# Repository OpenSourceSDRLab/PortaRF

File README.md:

# PortaRF
Custom Hardware and Firmware Bin Files for the PortaRF Gadget.

# Introduction
The PortaRF is an open-source hardware platform that combines the [HackRF One R10](https://github.com/greatscottgadgets/hackrf/tree/master/hardware/hackrf-one) and [PortaPack H4M](https://github.com/OpenSourceSDRLab/mayhem-firmware/tree/next/hardware/portapack_h4m) into a single Board. It supports the transmission and reception of radio signals ranging from 1 MHz to 6 GHz, rendering it an exceptionally versatile tool for RF exploration and development.  It is a portable, standalone device for signal analysis and transmission without requiring a computer.

Here is a news report about the PortaRF from [RTL-SDR.com](https://www.rtl-sdr.com/two-youtube-reviews-of-the-new-portarf-a-new-hackrf-portapack-combo/).

# Where to buy
[OpenSourceSDRLab](https://opensourcesdrlab.com/products/portarf) official website.

# Videos

)

# Hardware Improvements
1. **Doubled flash storage capacity**.
We have replaced the original W25Q80DVSSIQ with W25Q16DV SPI Flash chip, expanding the original firmware storage capacity from 1M byte to 2M byte. This provides a broader creative space for Mayhem firmware developers, enabling the implementation of more complex signal processing algorithms and functions.

2. **4.0-inch IPS resistive touch screen**.
The screen has been upgraded to a 4.0-inch IPS full-view high-definition display. Compared with the original 3.2-inch non-IPS matte screen, it has made a significant improvement in color reproduction, viewing angle and touch accuracy. Whether it's spectrum analysis or parameter settings, the text is clearer and the operation is more precise.

3. **3000mAh lithium battery system**.
The battery capacity has been increased to 3000mAh, significantly extending the battery life. At the same time, an intelligent battery protection board has been used in this battery, providing protection against overcharging, overdischarging, short circuiting, and overcurrent. This lithium battery is produced by a legitimate factory with guaranteed quality.

4. **User-friendly hand-held directional keys**.
PortaRF has added a gamepad-style directional button. It is particularly suitable for rapid directional operations in functions such as spectrum scanning and game applications. It will significantly enhance the direction control efficiency and comfort.

5. **Modular Expansion Board Design**.
The expansion board adopts a Board to Board connector, a socket interface similar to the memory module, which is smaller in size and more stable in installation. This can optimize the internal space utilization.

6. **Light Guide Column LED Status Indication System**.
PortaRF also incorporates the light guide column design, making the LED status lights more visible. Regardless of day or night, the equipment status is clearly visible.

7. **Nice shell design**.
We have designed a brand new shell for the PortaRF and added many design elements, such as the buckle of the shell, which makes the shell fit tightly. The slot of the memory card is designed with grooves, the SD card can be inserted and removed without the need for tools. The dual speaker sound hole design enables better sound output from the speakers.

8. **AI voice-assisted (Beta version)**.
PortaRF incorporates voice-controlled interaction technology. Users can perform operations such as device activation, application switching, and system reboot through natural voice commands. This feature is particularly suitable for scenarios where hands are not available, providing additional convenience operations.

# Applications
<div class="editor_table_wrap">&nbsp;
<table border="1" style="width: 81.0373%; height: 526px;">
<tbody>
<tr style="height: 26.2px;">
<td style="width: 55.25%; height: 26.2px;">
<h3 class="text-xl font-semibold text-indigo-800 mb-3">Receive Applications</h3>
</td>
<td style="width: 44.7339%; height: 26.2px;">
<h3 class="text-xl font-semibold text-indigo-800 mb-3">Transmit Applications</h3>
</td>
</tr>
<tr style="height: 22.4px;">
<td style="width: 55.25%; height: 22.4px;"><strong>Sniff &amp; Capture</strong>: Sniff &amp; capture signals for instant replay or save to SD card for analysis</td>
<td style="width: 44.7339%; height: 22.4px;"><strong>ADS-B</strong>: Transmit ADS-B (Aviation) signals for testing</td>
</tr>
<tr style="height: 44.8px;">
<td style="width: 55.25%; height: 44.8px;"><strong>ADS-B</strong>: Receive and analyze aviation signals with real-time location display</td>
<td style="width: 44.7339%; height: 44.8px;"><strong>APRS</strong>: Transmit APRS packets for GPS, weather stations and telemetry</td>
</tr>
<tr style="height: 22.4px;">
<td style="width: 55.25%; height: 22.4px;"><strong>AIS</strong>: Receive and analyze marine vessel signals</td>
<td style="width: 44.7339%; height: 22.4px;"><strong>GPS</strong>: Transmit GPS signals for testing</td>
</tr>
<tr style="height: 22.4px;">
<td style="width: 55.25%; height: 22.4px;"><strong>AFSK</strong>: Receive, demodulate and analyze AFSK signals</td>
<td style="width: 44.7339%; height: 22.4px;"><strong>Key Fob</strong>: Key-fob capture, replay and emulation for multiple models</td>
</tr>
<tr style="height: 22.4px;">
<td style="width: 55.25%; height: 22.4px;"><strong>Bluetooth</strong>: Sniff MAC addresses of BLE devices</td>
<td style="width: 44.7339%; height: 22.4px;"><strong>Morse Code</strong>: Morse code transmission tool</td>
</tr>
<tr style="height: 22.4px;">
<td style="width: 55.25%; height: 22.4px;"><strong>NRF</strong>: Decode NRF24L01 signals, commonly used for drones</td>
<td style="width: 44.7339%; height: 22.4px;"><strong>Burger Pager</strong>: Transmit restaurant pager signals</td>
</tr>
<tr style="height: 22.4px;">
<td style="width: 55.25%; height: 22.4px;"><strong>Audio</strong>: Decode WFM/NFM/AM radio transmissions</td>
<td style="width: 44.7339%; height: 22.4px;"><strong>POCSAG</strong>: Transmit pager signals</td>
</tr>
<tr style="height: 22.4px;">
<td style="width: 55.25%; height: 22.4px;"><strong>Spectrum Analyzer</strong>: Waterfall spectrum analyzer for detecting signals</td>
<td style="width: 44.7339%; height: 22.4px;"><strong>SSTV</strong>: Transmit Slow Scan Television signals</td>
</tr>
<tr style="height: 22.4px;">
<td style="width: 55.25%; height: 22.4px;"><strong>Analog TV</strong>: Decode and watch analog TV signals, used on FPV drones</td>
<td style="width: 44.7339%; height: 22.4px;"><strong>RDS</strong>: Send Radio Data System messages</td>
</tr>
<tr style="height: 22.4px;">
<td style="width: 55.25%; height: 22.4px;"><strong>ERT Meters</strong>: Decode ERT Meter signals</td>
<td style="width: 44.7339%; height: 22.4px;"><strong>OOK</strong>: Send On-Off Keying packages</td>
</tr>
<tr style="height: 22.4px;">
<td style="width: 55.25%; height: 22.4px;"><strong>POCSAG</strong>: Sniff and decode pager signals</td>
<td style="width: 44.7339%; height: 22.4px;"></td>
</tr>
<tr style="height: 22.4px;">
<td style="width: 55.25%; height: 22.4px;"><strong>Radiosonde</strong>: Sniff and decode weather station signals</td>
<td style="width: 44.7339%; height: 22.4px;"></td>
</tr>
<tr style="height: 22.4px;">
<td style="width: 55.25%; height: 22.4px;"><strong>TPMS</strong>: Decode Tire Pressure Monitoring System sensors</td>
<td style="width: 44.7339%; height: 22.4px;">&nbsp; &nbsp; &nbsp; &nbsp;</td>
</tr>
</tbody>
</table>

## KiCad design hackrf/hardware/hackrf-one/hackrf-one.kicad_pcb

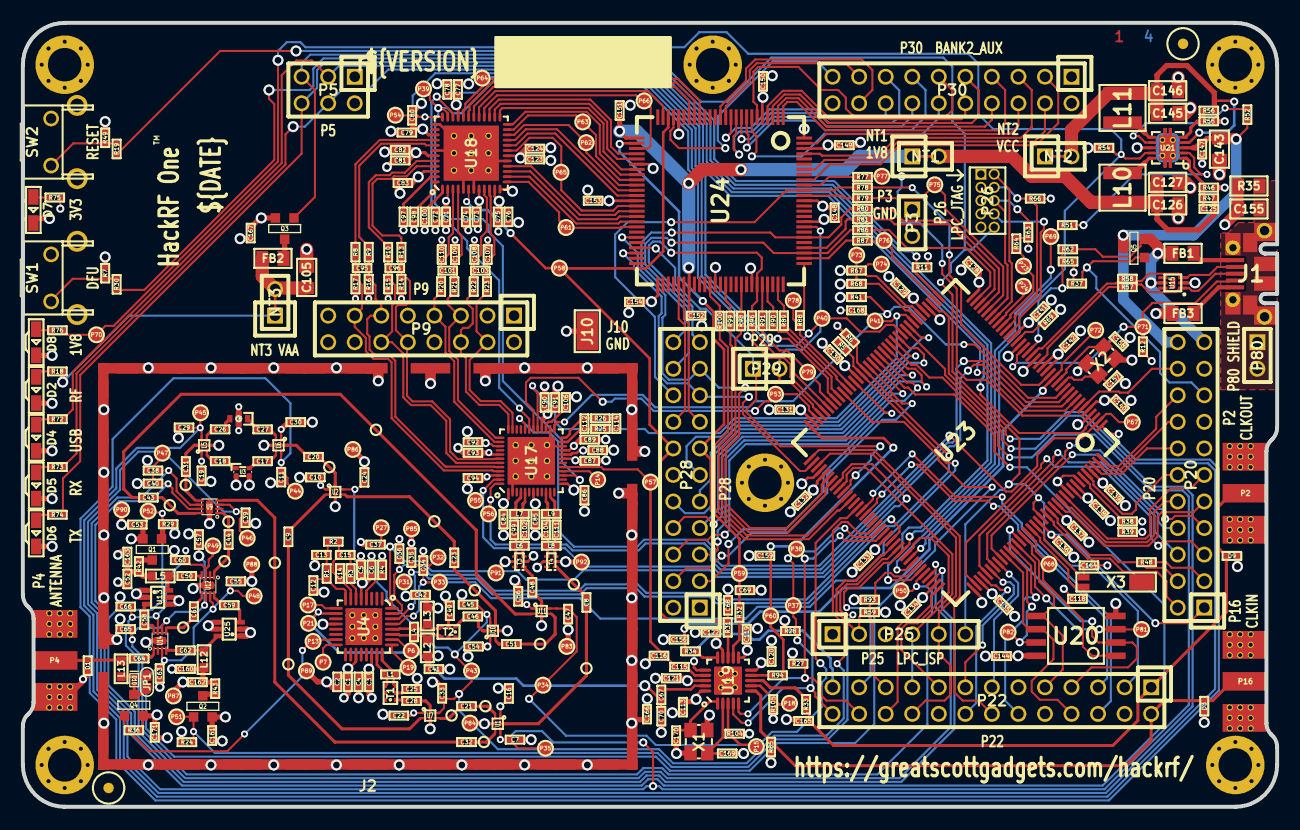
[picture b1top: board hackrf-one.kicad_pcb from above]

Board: 4 copper layers, 120.0 x 75.0 mm, 437 parts (0 on the bottom side), 319 nets.

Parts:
C1, C3, C5, C7, C11, C24, C29, C33, C34, C35, C36, C37, C38, C39, C40, C45, C47, C55, C57, C60, C63, C65, C66, C67, C115, C125: 33pF; GSG-0402
C2, C4, C6, C10, C16, C19, C22, C30, C54, C56, C87, C88, C89, C92, C93, C162, C163: 10nF; GSG-0402
C8, C21, C32, C43, C48, C51, C84, C85, C86, C94, C95, C96, C99, C101, C102, C103, C107, C108, C109, C110: 22pF; GSG-0402
C9, C17, C18, C20, C23, C25, C28, C31, C44, C46, C49, C50, C58, C59, C61, C62, C64, C71, C73, C75, C77, C79, C81, C83, C91, C113, C119, C120, C121, C122, C123, C128, C129, C130, C131, C132, C133, C134, C135, C136, C137, C138, C139, C140, C141, C142, C144, C147, C148, C149, C150, C151, C152, C153, C154, C166, C167: 100nF; GSG-0402
C12, C13: 330pF; GSG-0402
C14: 8p2; GSG-0402
C15, C112: 180pF; GSG-0402
C26, C27, C116, C156: 47pF; GSG-0402
C41, C42, C52, C68, C69, C70, C90, C159, C160, C165, C168: 100pF; GSG-0402
C53, C106, C161, C171: 1uF; GSG-0402
C72, C74, C76, C78, C80, C82, C124: 2.2uF; GSG-0402
C97, C98, C100: 330nF; GSG-0402
C104, C111: 3pF; GSG-0402
C105, C126, C127, C143, C145, C146: 10uF; GSG-0805
C114: 3.3nF; GSG-0402
C118, C157, C158, C164: 18pF; GSG-0402
C155: DNP; GSG-0805
C169, C170: 1.8pF; GSG-0402
D1, D3, D9: GSG-DIODE-TVS-BI; GSG-0402
D2: VAALED; LTST-S220
D4: USBLED; LTST-S220
D5: RXLED; LTST-S220
D6: TXLED; LTST-S220
D7: VCCLED; LTST-S220
D8: 1V8LED; LTST-S220
D10: D_Schottky; DSN1006-2
FB1, FB2, FB3: FILTER; GSG-0805
FID1, FID2: FIDUCIAL; GSG-MARK1MM
J1: USB-MICRO-B; GSG-USB-MICROB-FCI-10103592-EXT
J2: RF-SHIELD-FRAME; GSG-SHIELD-BMI-S-230
J4, J5, J6, J7, J8, J9: MOUNTING_HOLE; GSG-HOLE126MIL-COPPER
J10: GND_CLIP; GSG-TEST-POINT-S1751-46R
JP1: Jumper; 0603-JUMPER
L1, L4, L6, L8, L9: DNP; GSG-0402
L2, L3, L5, L12, L13: 10uH; GSG-0603
L7: 6.2nH; GSG-0402
L10, L11: 4u7; GSG-NRG4026
NT1: 1V8; HEADER-1x2-SHORTED
NT2: VCC; HEADER-1x2-SHORTED
NT3: VAA; HEADER-1x2-SHORTED
P2: CLKOUT; GSG-SMA-73251-2120
P3: GND; GSG-HEADER-NOMARK-1x2
P4: ANTENNA; GSG-SMA-73251-2120
P5: LEDS; GSG-HEADER-2x3
P6: GPO4; GSG-TESTPOINT-50MIL
P7: GPO2; GSG-TESTPOINT-50MIL
P9: BASEBAND; GSG-HEADER-2x8
P13: GPO1; GSG-TESTPOINT-50MIL
P14: XCVR_CLKOUT; GSG-TESTPOINT-50MIL
P15: INTR; GSG-TESTPOINT-50MIL
P16: CLKIN; GSG-SMA-73251-2120
P17: GPO6; GSG-TESTPOINT-50MIL
P18: OEB; GSG-TESTPOINT-50MIL
P19: GPO3; GSG-TESTPOINT-50MIL
P20: GPIO; GSG-HEADER-2x11
P21: REF_IN; GSG-TESTPOINT-50MIL
P22: I2S; GSG-HEADER-2x13
P23: DBGEN; GSG-TESTPOINT-50MIL
P24: TRST; GSG-TESTPOINT-50MIL
P25: LPC_ISP; GSG-HEADER-1x6
P26: LPC_JTAG; GSG-50MIL-HEADER-2x5-TH
P27: MIXER_SDATA; GSG-TESTPOINT-50MIL
P28: SD; GSG-HEADER-2x11
P29: CPLD_JTAG; GSG-HEADER-1x2
P30: BANK2_AUX; GSG-HEADER-2x10
P31: MIXER_SCLK; GSG-TESTPOINT-50MIL
P32: MIXER_ENX; GSG-TESTPOINT-50MIL
P33: MIXER_RESETX; GSG-TESTPOINT-50MIL
P34: MIX_BYPASS; GSG-TESTPOINT-50MIL
P35: !MIX_BYPASS; GSG-TESTPOINT-50MIL
P37: SCL; GSG-TESTPOINT-50MIL
P38: SDA; GSG-TESTPOINT-50MIL
P39: SSP1_SCK; GSG-TESTPOINT-50MIL
P40: SSP1_COPI; GSG-TESTPOINT-50MIL
P41: SSP1_CIPO; GSG-TESTPOINT-50MIL
P43: RX; GSG-TESTPOINT-50MIL
P44: HP; GSG-TESTPOINT-50MIL
P45: LP; GSG-TESTPOINT-50MIL
P46: TX_MIX_BP; GSG-TESTPOINT-50MIL
P47: RX_MIX_BP; GSG-TESTPOINT-50MIL
P48: TX_AMP; GSG-TESTPOINT-50MIL
P49: RX_AMP; GSG-TESTPOINT-50MIL
P50: AMP_BYPASS; GSG-TESTPOINT-50MIL
P51: !TX_AMP_PWR; GSG-TESTPOINT-50MIL
P52: !RX_AMP_PWR; GSG-TESTPOINT-50MIL
P53: CS_XCVR; GSG-TESTPOINT-50MIL
P54: CS_AD; GSG-TESTPOINT-50MIL
P55: TXENABLE; GSG-TESTPOINT-50MIL
P56: RXENABLE; GSG-TESTPOINT-50MIL
P57: XTAL2; GSG-TESTPOINT-50MIL
P58: GCK1; GSG-TESTPOINT-50MIL
P59: GCK2; GSG-TESTPOINT-50MIL
P60: SGPIO_CLK; GSG-TESTPOINT-50MIL
P61: DA0; GSG-TESTPOINT-50MIL
P62: DA7; GSG-TESTPOINT-50MIL
P63: DD0; GSG-TESTPOINT-50MIL
P64: DD9; GSG-TESTPOINT-50MIL
P65: DA4; GSG-TESTPOINT-50MIL
P66: DD5; GSG-TESTPOINT-50MIL
P67: RSSI; GSG-TESTPOINT-50MIL
P68: SPIFI_CS; GSG-TESTPOINT-50MIL
P69: VREGMODE; GSG-TESTPOINT-50MIL
P70: EN_1V8; GSG-TESTPOINT-50MIL
P71: ID; GSG-TESTPOINT-50MIL
P72: GP_CLKIN; GSG-TESTPOINT-50MIL
P73: P1_2; GSG-TESTPOINT-50MIL
P74: P1_1; GSG-TESTPOINT-50MIL
P75: SGPIO0; GSG-TESTPOINT-50MIL
P76: SGPIO7; GSG-TESTPOINT-50MIL
P77: SGPIO9; GSG-TESTPOINT-50MIL
P78: SGPIO10; GSG-TESTPOINT-50MIL
P79: SGPIO11; GSG-TESTPOINT-50MIL
P80: SHIELD; GSG-HEADER-NOMARK-1x2
P81: SPIFI_SIO2; GSG-TESTPOINT-50MIL
P82: SPIFI_SIO3; GSG-TESTPOINT-50MIL
P83, P84, P85, P86, P87, P88, P89, P90, P91, P92: GND; GSG-TESTPOINT-50MIL
Q1, Q2, Q3, Q4, Q5: MOSFET_P; SOT23-3
R1, R2, R72, R75: 470; GSG-0402
R3: 22k; GSG-0402
R4: 51k; GSG-0402
R5, R6, R7, R11, R12, R24, R29, R36, R37, R41, R48, R49, R51, R52, R54, R59, R62, R63, R64, R66, R67, R68, R85, R93, R104, R105: 10k; GSG-0402
R8, R9, R10, R13, R73, R76: 1k; GSG-0402
R14, R15, R16, R17: 4k7; GSG-0402
R18, R27, R28, R74: 1k8; GSG-0402
R19, R30, R31, R32, R33, R34, R77, R78, R79, R80, R81, R86, R87, R88, R89, R90, R91, R94, R96, R98, R99, R100: 39; GSG-0402
R20, R21, R22, R23, R57, R58: 0; GSG-0402
R25, R26: 475; GSG-0402
R35: DNP; GSG-0805
R38: 15.4k; GSG-0402
R39, R47: 330k; GSG-0402
R42, R43: 18; GSG-0402
R46, R55: 162k; GSG-0402
R56: 715k; GSG-0402
R65: 18k; GSG-0402
R69: 12k; GSG-0402
SW1: DFU; GSG-SWITCH-FSMRA
SW2: RESET; GSG-SWITCH-FSMRA
T1: MIX_IN_BALUN; GSG-B0310J50100AHF
T2: MIX_OUT_BALUN; GSG-B0310J50100AHF
T3: RX_BALUN; GSG-2500BL14M100
T4: TX_BALUN; GSG-2500BL14M100
TESTPOINT-30MIL-MASKONLY, TESTPOINT-30MIL-MASKONLY#2, TESTPOINT-30MIL-MASKONLY#3, TESTPOINT-30MIL-MASKONLY#4, TESTPOINT-30MIL-MASKONLY#5, TESTPOINT-30MIL-MASKONLY#6, TESTPOINT-30MIL-MASKONLY#7, TESTPOINT-30MIL-MASKONLY#8, TESTPOINT-30MIL-MASKONLY#9, TESTPOINT-30MIL-MASKONLY#10, TESTPOINT-30MIL-MASKONLY#11, TESTPOINT-30MIL-MASKONLY#12, TESTPOINT-30MIL-MASKONLY#13, TESTPOINT-30MIL-MASKONLY#14, TESTPOINT-30MIL-MASKONLY#15, TESTPOINT-30MIL-MASKONLY#16, TESTPOINT-30MIL-MASKONLY#17: VAL**; GSG-TESTPOINT-30MIL-MASKONLY
U1, U2, U5, U6, U7, U10, U11: SKY13453; SKY13350-385LF
U3: LOWPASS_FILTER; GSG-LP0603
U4: RFFC5072; GSG-QFN32
U8: HIGHPASS_FILTER; GSG-HP-DEA
U9, U12, U14: SKY13317; GSG-SKY13317-373LF
U13, U25: MGA-81563; GSG-SOT363
U15: TVS; GSG-LXES1TBCC2-004
U17: MAX2837; GSG-QFN48-6
U18: MAX5864; GSG-QFN48-7
U19: SI5351C; GSG-QFN20-4
U20: W25Q80; GSG-SOIC8-208
U21: TPS62410; GSG-S-PVSON-N10
U23: LPC4320FBD144; GSG-LQFP144
U24: GSG-XC2C64A-7VQG100C; GSG-VQ100
X1: MAIN_XTAL; GSG-XTAL3.2x2.5mm
X2: MCU_XTAL; GSG-XTAL3.2x2.5mm
X3: RTC_XTAL; GSG-XTAL-AB26TRQ

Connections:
!MIX_BYPASS: C7.2, C38.2, P35.1, U1.5 (VCTL), U9.6 (V2), U23.50 (P1_7)
!RX_AMP_PWR: P52.1, Q1.1 (G), R29.2, U23.106 (P2_12)
!TX_AMP_PWR: P51.1, Q2.1 (G), R24.1, U23.97 (P6_9)
!VAA_ENABLE: P5.5, Q3.1 (G), R11.2, U23.37 (P5_0)
+1V8: C151.1, C152.1, NT1.1, U24.26 (VCC), U24.57 (VCC)
/baseband/CLK0: R31.2, U19.13 (CLK0)
/baseband/CLK1: R32.2, U19.12 (CLK1)
/baseband/CLK2: R94.2, U19.9 (CLK2)
/baseband/CLK3: R33.2, U19.8 (CLK3)
/baseband/CLK5: C115.1, U19.17 (CLK5)
/baseband/COM: C97.1, U18.47 (COM)
/baseband/CPOUT+: C112.2, R25.1, U17.23 (CPOUT+)
/baseband/CPOUT-: C112.1, R26.1, U17.24 (CPOUT-)
/baseband/IA+: C101.1, C110.1, R20.1, U18.3 (IA+)
/baseband/IA-: C101.2, C109.1, R21.1, U18.4 (IA-)
/baseband/ID+: R13.1, U18.45 (ID+)
/baseband/ID-: R10.1, U18.44 (ID-)
/baseband/INTR: P15.1, R104.2, U19.3 (INTR)
/baseband/OEB: P18.1, R105.2, U19.7 (OEB)
/baseband/QA+: C103.2, C107.1, R23.1, U18.10 (QA+)
/baseband/QA-: C103.1, C108.1, R22.1, U18.9 (QA-)
/baseband/QD+: R8.1, U18.40 (QD+)
/baseband/QD-: R9.1, U18.41 (QD-)
/baseband/REFN: C98.1, U18.48 (REFN)
/baseband/REFP: C100.1, U18.1 (REFP)
/baseband/RXBBI+: P9.7, R20.2, U17.38 (RXBBI+)
/baseband/RXBBI-: P9.5, R21.2, U17.37 (RXBBI-)
/baseband/RXBBQ+: P9.6, R22.2, U17.36 (RXBBQ+)
/baseband/RXBBQ-: P9.4, R23.2, U17.35 (RXBBQ-)
/baseband/TXBBI+: C96.1, P9.12, R10.2, R15.1, U17.43 (TXBBI+)
/baseband/TXBBI-: C96.2, P9.10, R13.2, R14.1, U17.42 (TXBBI-)
/baseband/TXBBQ+: C95.2, P9.11, R9.2, R16.1, U17.44 (TXBBQ+)
/baseband/TXBBQ-: C95.1, P9.13, R8.2, R17.1, U17.45 (TXBBQ-)
/baseband/XA: C170.2, U19.1 (XA), X1.3
/baseband/XB: C169.2, U19.2 (XB), X1.1
/baseband/XCVR_CLKOUT: P14.1, U17.16 (CLOCKOUT)
/baseband/XTAL2: C115.2, C116.1, P57.1, U17.17 (XTAL2)
/frontend/!ANT_BIAS: P13.1, Q4.1 (G), R36.1, U4.15 (GPO1/ADD1)
/frontend/REF_IN: C67.2, C70.1, P21.1, U4.10 (REF_IN)
/frontend/RX_AMP_IN: C58.1, U14.8 (RF3)
/frontend/RX_AMP_OUT: C50.2, U12.4 (RF1)
/frontend/TX_AMP_IN: C59.1, U12.8 (RF3)
/frontend/TX_AMP_OUT: C62.1, U14.4 (RF1)
/mcu/usb/power/ADC0_0: P20.20, U23.6 (ADC0_0/ADC1_0/DAC)
/mcu/usb/power/ADC0_2: P20.16, U23.143 (ADC0_2/ADC1_2)
/mcu/usb/power/ADC0_3: R38.2, R39.1, U23.139 (ADC0_3/ADC1_3)
/mcu/usb/power/ADC0_5: P20.18, U23.144 (ADC0_5/ADC1_5)
/mcu/usb/power/ADC0_6: P20.14, U23.142 (ADC0_6/ADC1_6)
/mcu/usb/power/B1AUX13: P28.16, U24.55 (BANK1F4M13)
/mcu/usb/power/B1AUX14: P28.15, U24.56 (BANK1F4M14)
/mcu/usb/power/B2AUX1: P30.18, U24.13 (BANK2F1M1)
/mcu/usb/power/B2AUX2: P30.17, U24.12 (BANK2F1M2)
/mcu/usb/power/B2AUX3: P30.16, U24.11 (BANK2F1M3)
/mcu/usb/power/B2AUX4: P30.15, U24.10 (BANK2F1M4)
/mcu/usb/power/B2AUX5: P30.14, U24.9 (BANK2F1M5)
/mcu/usb/power/B2AUX6: P30.13, U24.8 (BANK2F1M6)
/mcu/usb/power/B2AUX7: P30.12, U24.7 (BANK2F1M7)
/mcu/usb/power/B2AUX8: P30.11, U24.6 (BANK2F1M8)
/mcu/usb/power/B2AUX9: P30.10, U24.4 (BANK2F1M9)
/mcu/usb/power/B2AUX10: P30.9, U24.3 (BANK2F1M10)
/mcu/usb/power/B2AUX11: P30.8, U24.2 (BANK2F1M11)
/mcu/usb/power/B2AUX12: P30.7, U24.1 (BANK2F1M12)
/mcu/usb/power/B2AUX13: P30.6, U24.99 (BANK2F1M13)
/mcu/usb/power/B2AUX14: P30.5, U24.97 (BANK2F1M14)
/mcu/usb/power/B2AUX15: P30.4, U24.94 (BANK2F1M15)
/mcu/usb/power/B2AUX16: P30.3, U24.92 (BANK2F1M16)
/mcu/usb/power/BANK2F3M1: R77.2, U24.91 (BANK2F3M1)
/mcu/usb/power/BANK2F3M2: P28.18, R78.2, U24.90 (BANK2F3M2)
/mcu/usb/power/BANK2F3M3: R79.2, U24.89 (BANK2F3M3)
/mcu/usb/power/BANK2F3M4: P28.22, R80.2, U24.81 (BANK2F3M4)
/mcu/usb/power/BANK2F3M5: R81.2, U24.79 (BANK2F3M5)
/mcu/usb/power/BANK2F3M6: P28.20, R86.2, U24.78 (BANK2F3M6)
/mcu/usb/power/BANK2F3M7: R87.2, U24.77 (BANK2F3M7)
/mcu/usb/power/BANK2F3M8: R88.2, U24.76 (BANK2F3M8)
/mcu/usb/power/BANK2F3M9: R89.2, U24.74 (BANK2F3M9)
/mcu/usb/power/BANK2F3M10: R90.2, U24.72 (BANK2F3M10)
/mcu/usb/power/BANK2F3M11: R91.2, U24.71 (BANK2F3M11)
/mcu/usb/power/BANK2F3M12: P28.21, R96.2, U24.70 (BANK2F3M12)
/mcu/usb/power/BANK2F3M14: R98.2, U24.67 (BANK2F3M14)
/mcu/usb/power/BANK2F3M15: R99.2, U24.64 (BANK2F3M15)
/mcu/usb/power/BANK2F3M16: R100.2, U24.61 (BANK2F3M16)
/mcu/usb/power/CPLD_TCK: P28.17, U23.74 (P6_1), U24.48 (TCK)
/mcu/usb/power/CPLD_TDI: P28.19, U23.78 (P6_2), U24.45 (TDI)
/mcu/usb/power/CPLD_TDO: P29.2, U23.69 (P9_5), U24.83 (TDO)
/mcu/usb/power/CPLD_TMS: P29.1, U23.82 (P6_5), U24.47 (TMS)
/mcu/usb/power/DBGEN: P23.1, R64.1, U23.28 (DBGEN)
/mcu/usb/power/DM: R58.1, U23.20 (USB0_DM)
/mcu/usb/power/DP: R57.1, U23.18 (USB0_DP)
/mcu/usb/power/EN1V8: P70.1, R54.2, R76.2, U21.9 (EN2), U23.100 (P6_10)
/mcu/usb/power/GCK0: P30.19, U24.22 (BANK1F2M7)
/mcu/usb/power/GPIO3_8: P20.5, U23.110 (P7_0)
/mcu/usb/power/GPIO3_9: P20.6, U23.113 (P7_1)
/mcu/usb/power/GPIO3_10: P20.7, U23.115 (P7_2)
/mcu/usb/power/GPIO3_11: P20.8, U23.117 (P7_3)
/mcu/usb/power/GPIO3_12: P20.9, U23.132 (P7_4)
/mcu/usb/power/GPIO3_13: P20.10, U23.133 (P7_5)
/mcu/usb/power/GPIO3_14: P20.11, U23.134 (P7_6)
/mcu/usb/power/GPIO3_15: P20.12, U23.140 (P7_7)
/mcu/usb/power/GP_CLKIN: C156.1, P72.1, R34.1, U23.14 (P4_7)
/mcu/usb/power/I2C1_SCL: P22.5, U23.88 (P2_4)
/mcu/usb/power/I2C1_SDA: P22.6, U23.87 (P2_3)
/mcu/usb/power/I2S0_RX_MCLK: P22.14, U23.73 (P6_0)
/mcu/usb/power/I2S0_RX_SCK: P22.12, U23.120 (PF_4)
/mcu/usb/power/I2S0_RX_SDA: P22.13, U23.116 (P3_2)
/mcu/usb/power/I2S0_RX_WS: P22.15, U23.114 (P3_1)
/mcu/usb/power/I2S0_TX_MCLK: P22.17, U23.99 (CLK2)
/mcu/usb/power/I2S0_TX_SCK: P22.16, U23.112 (P3_0)
/mcu/usb/power/ISP: P25.2, R59.2, U23.96 (P2_7)
/mcu/usb/power/LED1: P5.3, R72.2, U23.3 (P4_1)
/mcu/usb/power/LED2: P5.4, R73.2, U23.8 (P4_2)
/mcu/usb/power/LED3: P5.6, R74.2, U23.103 (P6_12)
/mcu/usb/power/P1_1: P74.1, R67.1, U23.42 (P1_1)
/mcu/usb/power/P1_2: P73.1, R68.1, U23.43 (P1_2)
/mcu/usb/power/P2_8: P22.23, R30.1, U23.98 (P2_8)
/mcu/usb/power/P2_9: P22.21, R93.1, U23.102 (P2_9)
/mcu/usb/power/P2_13: P22.22, U23.108 (P2_13)
/mcu/usb/power/REG_OUT1: C145.2, C146.2, L11.1, NT2.2, R56.1, U21.4 (FB1)
/mcu/usb/power/REG_OUT2: C125.1, C126.1, C127.1, L10.2, NT1.2, R47.1
/mcu/usb/power/RESET: P22.3, P25.6, P26.10, R19.1, U23.128 (RESET)
/mcu/usb/power/RREF: R69.1, U23.24 (USB0_RREF)
/mcu/usb/power/RTCX1: C118.1, U23.125 (RTCX1), X3.2
/mcu/usb/power/RTCX2: C164.1, U23.126 (RTCX2), X3.1
/mcu/usb/power/RTC_ALARM: P20.2, U23.129 (RTC_ALARM)
/mcu/usb/power/SD_CD: P28.3, U23.60 (P1_13)
/mcu/usb/power/SD_CLK: P28.11, U23.45 (CLK0)
/mcu/usb/power/SD_CMD: P28.9, U23.49 (P1_6)
/mcu/usb/power/SD_DAT0: P28.7, U23.52 (P1_9)
/mcu/usb/power/SD_DAT1: P28.6, U23.53 (P1_10)
/mcu/usb/power/SD_DAT2: P28.5, U23.55 (P1_11)
/mcu/usb/power/SD_DAT3: P28.4, U23.56 (P1_12)
/mcu/usb/power/SD_POW: P28.10, U23.48 (P1_5)
/mcu/usb/power/SD_VOLT0: P28.8, U23.51 (P1_8)
/mcu/usb/power/SGPIO0: P75.1, R79.1, U23.32 (P0_0)
/mcu/usb/power/SGPIO1: R81.1, U23.34 (P0_1)
/mcu/usb/power/SGPIO2: R89.1, U23.62 (P1_15)
/mcu/usb/power/SGPIO3: R90.1, U23.64 (P1_16)
/mcu/usb/power/SGPIO4: R98.1, U23.79 (P6_3)
/mcu/usb/power/SGPIO5: R99.1, U23.83 (P6_6)
/mcu/usb/power/SGPIO6: R100.1, U23.84 (P2_2)
/mcu/usb/power/SGPIO7: P76.1, R87.1, U23.38 (P1_0)
/mcu/usb/power/SGPIO9: P77.1, R77.1, U23.7 (P4_3)
/mcu/usb/power/SGPIO10: P78.1, R88.1, U23.61 (P1_14)
/mcu/usb/power/SGPIO11: P79.1, R91.1, U23.66 (P1_17)
/mcu/usb/power/SGPIO12: R96.1, U23.67 (P1_18)
/mcu/usb/power/SGPIO13: R78.1, U23.15 (P4_8)
/mcu/usb/power/SGPIO14: R80.1, U23.33 (P4_9)
/mcu/usb/power/SGPIO15: R86.1, U23.35 (P4_10)
/mcu/usb/power/SPIFI_CIPO: P22.7, U20.2 (DO), U23.122 (P3_6)
/mcu/usb/power/SPIFI_COPI: P22.9, U20.5 (DI), U23.123 (P3_7)
/mcu/usb/power/SPIFI_CS: P68.1, U20.1 (CS), U23.124 (P3_8)
/mcu/usb/power/SPIFI_SCK: P22.8, U20.6 (CLK), U23.118 (P3_3)
/mcu/usb/power/SPIFI_SIO2: P81.1, U20.3 (WP), U23.121 (P3_5)
/mcu/usb/power/SPIFI_SIO3: P82.1, U20.7 (HOLD), U23.119 (P3_4)
/mcu/usb/power/TCK: P26.4, R66.2, U23.27 (TCK/SWDCLK)
/mcu/usb/power/TDI: P26.8, U23.26 (TDI)
/mcu/usb/power/TDO: P26.6, R63.1, U23.31 (TDO/SWO)
/mcu/usb/power/TMS: P26.2, U23.30 (TMS/SWDIO)
/mcu/usb/power/U0_RXD: P22.19, P25.4, U23.81 (P2_1)
/mcu/usb/power/U0_TXD: P22.20, P25.5, U23.75 (P2_0)
/mcu/usb/power/USB_SHIELD: C155.1, J1.0 (SHIELD), P80.1, P80.2, R35.1
/mcu/usb/power/VBAT: C136.1, P20.1, U23.127 (VBAT)
/mcu/usb/power/VBUS: FB1.2, P20.21, Q5.2 (S), R62.2, U15.5 (VDD)
/mcu/usb/power/VBUSCTRL: P20.17, Q5.1 (G), R37.2
/mcu/usb/power/VIN: C143.1, C147.1, P20.22, Q5.3 (D), R52.1, U21.3 (VIN)
/mcu/usb/power/VREGMODE: P69.1, R51.2, U23.101 (P6_11)
/mcu/usb/power/WAKEUP: P20.4, R48.2, U23.130 (WAKEUP0)
/mcu/usb/power/XTAL1: C157.1, U23.12 (XTAL1), X2.1
/mcu/usb/power/XTAL2: C158.1, U23.13 (XTAL2), X2.3
AMP_BYPASS: C57.1, C65.2, P50.1, U12.6 (V2), U14.6 (V2), U23.104 (P2_10)
CLK6: P22.25, U19.16 (CLK6)
CLKIN: D3.2 (K), P16.1 (RF), P22.2, R85.1, U19.6 (CLKIN)
CLKOUT: C165.1, D9.2 (K), P2.1 (RF), P22.1, R33.1
CS_AD: P54.1, U18.36 (CS), U23.65 (P5_7)
CS_XCVR: P53.1, U17.30 (CS), U23.70 (P1_20)
DA0: P61.1, U18.13 (DA0), U24.43 (BANK1F4M8)
DA1: U18.14 (DA1), U24.42 (BANK1F4M7)
DA2: U18.15 (DA2), U24.41 (BANK1F4M6)
DA3: U18.16 (DA3), U24.40 (BANK1F4M5)
DA4: P65.1, U18.19 (DA4), U24.39 (BANK1F4M4)
DA5: U18.20 (DA5), U24.37 (BANK1F4M3)
DA6: U18.21 (DA6), U24.36 (BANK1F4M2)
DA7: P62.1, U18.22 (DA7), U24.35 (BANK1F4M1)
DD0: P63.1, U18.23 (DD0), U24.34 (BANK1F2M16)
DD1: U18.24 (DD1), U24.33 (BANK1F2M15)
DD2: U18.25 (DD2), U24.32 (BANK1F2M14)
DD3: U18.26 (DD3), U24.30 (BANK1F2M13)
DD4: U18.27 (DD4), U24.29 (BANK1F2M12)
DD5: P66.1, U18.28 (DD5), U24.28 (BANK1F2M11)
DD6: U18.29 (DD6), U24.24 (BANK1F2M9)
DD7: U18.30 (DD7), U24.19 (BANK1F2M6)
DD8: U18.31 (DD8), U24.18 (BANK1F2M5)
DD9: P64.1, U18.32 (DD9), U24.17 (BANK1F2M4)
GCK1: C68.1, P28.14, P58.1, R31.1, U18.6 (CLK), U24.23 (BANK1F2M8)
GCK2: C69.1, P28.13, P59.1, R32.1, U24.27 (BANK1F2M10)
GND: C1.2, C2.2, C3.2, C4.2, C5.2, C6.2, C7.1, C10.1, C11.1, C12.2, C13.2, C16.2, C19.1, C22.1, C24.1, C25.2, C29.2, C30.2, C33.2, C34.2, C35.2, C36.2, C37.2, C38.1, C39.1, C40.1, C41.2, C42.2, C45.1, C47.1, C49.1, C52.2, C53.2, C54.2, C55.2, C56.2, C57.2, C60.1, C63.2, C65.1, C66.1, C68.2, C69.2, C70.2, C71.2, C72.2, C73.2, C74.2, C75.2, C76.2, C77.2, C78.2, C79.2, C80.2, C81.2, C82.2, C83.2, C84.2, C85.2, C86.2, C87.2, C88.2, C89.2, C90.2, C91.2, C92.2, C93.2, C94.2, C97.2, C98.2, C100.2, C105.2, C106.2, C107.2, C108.2, C109.2, C110.2, C113.2, C116.2, C118.2, C119.2, C120.2, C121.2, C122.2, C123.2, C124.2, C126.2, C127.2, C128.2, C129.2, C130.2, C131.2, C132.2, C133.2, C134.2, C135.2, C136.2, C137.2, C138.2, C139.2, C140.2, C141.2, C142.2, C143.2, C144.2, C145.1, C146.1, C147.2, C148.2, C149.2, C150.2, C151.2, C152.2, C153.2, C154.2, C155.2, C156.2, C157.2, C158.2, C159.2, C160.2, C161.2, C162.1, C163.1, C164.2, C165.2, C166.2, C167.2, C168.2, C169.1, C170.1, C171.2, D1.1 (A), D2.1 (K), D3.1 (A), D4.1 (K), D5.1 (K), D6.1 (K), D7.1 (K), D8.1 (K), D9.1 (A), FB3.2, J2.0 (SHIELD), J4.1, J5.1, J6.1, J7.1, J8.1, J9.1, J10.1, P2.2 (GND), P3.1, P3.2, P4.2 (GND), P5.1, P9.1, P9.2, P9.3, P9.8, P9.9, P9.14, P9.15, P9.16, P16.2 (GND), P20.13, P20.15, P20.19, P22.4, P22.10, P22.18, P25.1, P26.3, P26.5, P26.9, P28.2, P28.12, P30.2, P30.20, P83.1, P84.1, P85.1, P86.1, P87.1, P88.1, P89.1, P90.1, P91.1, P92.1, R4.1, R7.2, R14.2, R15.2, R16.2, R17.2, R35.2, R37.1, R39.2, R41.1, R46.1, R54.1, R55.1, R65.1, R68.2, R69.2, R85.2, R93.2, SW1.0 (SHIELD), SW2.0 (SHIELD), SW2.1, T3.2 (PC), T3.5 (S2), T4.2 (PC), T4.5 (S2), U1.3 (GND), U2.3 (GND), U3.2 (GND), U3.3 (GND), U4.0 (EP), U4.12 (TM), U5.3 (GND), U6.3 (GND), U7.3 (GND), U8.2 (GND), U8.4 (GND), U9.0 (GND), U10.3 (GND), U11.3 (GND), U12.0 (GND), U13.1 (GND), U13.2 (GND), U13.4 (GND), U13.5 (GND), U14.0 (GND), U15.2 (GND), U17.0 (EP), U17.2 (GNDRXLNA), U17.22 (GNDCP), U17.26 (GNDVCO), U18.0 (EP), U18.5 (GND), U18.7 (GND), U18.12 (GND), U18.17 (OGND), U18.37 (GND), U18.42 (GND), U19.0 (GND), U20.4 (GND), U21.0 (PP), U21.8 (GND), U23.4 (VSSIO), U23.19 (USB0_VSSA_TERM), U23.23 (USB0_VSSA_REF), U23.40 (VSSIO), U23.76 (VSSIO), U23.109 (VSSIO), U23.135 (VSSA), U23.138 (ADC0_4/ADC1_4), U24.21 (GND), U24.31 (GND), U24.62 (GND), U24.69 (GND), U24.84 (GND), U24.100 (GND), U25.1 (GND), U25.2 (GND), U25.4 (GND), U25.5 (GND), X1.2, X1.4, X2.2, X2.4
HP: C11.2, P44.1, U6.5 (VCTL), U23.1 (P4_0)
LP: C29.1, P45.1, U5.5 (VCTL), U23.39 (P5_1)
MCU_CLK: R34.2, U19.15 (CLK7)
MIXER_ENX: C35.1, P32.1, R6.2, U4.30 (ENX), U23.57 (P5_4)
MIXER_RESETX: C34.1, P33.1, R5.2, U4.29 (RESETX), U23.58 (P5_5)
MIXER_SCLK: C36.1, P31.1, U4.31 (SCLK), U23.95 (P2_6)
MIXER_SDATA: C37.1, P27.1, U4.32 (SDATA), U23.80 (P6_4)
MIX_BYPASS: C47.2, P34.1, U11.5 (VCTL), U23.86 (P6_8)
MIX_CLK: C67.1, U19.19 (CLK4)
unnamed: C8.2, U1.6 (RFC)
unnamed: C9.1, U7.2 (RF1)
unnamed: C9.2, U2.2 (RF1)
unnamed: C12.1, R1.2, U4.8 (LFILT3)
unnamed: C13.1, R1.1, R2.2
unnamed: C14.1, C15.1, R2.1, U4.7 (LFITLT2)
unnamed: C14.2, R3.1, U4.6 (LFILT1)
unnamed: C15.2, R3.2
unnamed: C17.1, U3.4 (IN)
unnamed: C17.2, U6.4 (RF2)
unnamed: C18.1, U5.2 (RF1)
unnamed: C18.2, U3.1 (OUT)
unnamed: C20.1, U6.6 (RFC)
unnamed: C20.2, U2.6 (RFC)
unnamed: C21.1, U1.2 (RF1)
unnamed: C21.2, U7.4 (RF2)
unnamed: C23.1, U10.4 (RF2)
unnamed: C23.2, U2.4 (RF2)
unnamed: C25.1, T1.2 (S2)
unnamed: C26.1, U8.3 (OUT)
unnamed: C26.2, U5.4 (RF2)
unnamed: C27.1, U8.1 (IN)
unnamed: C27.2, U6.2 (RF1)
unnamed: C28.1, T1.1 (S1)
unnamed: C28.2, U7.6 (RFC)
unnamed: C31.1, U9.5 (RF2)
unnamed: C31.2, U5.6 (RFC)
unnamed: C32.1, U1.4 (RF2)
unnamed: C32.2, U9.4 (RF1)
unnamed: C43.1, U9.8 (RF3)
unnamed: C43.2, U11.2 (RF1)
unnamed: C44.1, U12.1 (RFC)
unnamed: C44.2, U9.1 (RFC)
unnamed: C46.1, U10.6 (RFC)
unnamed: C46.2, T2.1 (S1)
unnamed: C48.1, U11.6 (RFC)
unnamed: C49.2, T2.2 (S2)
unnamed: C50.1, L5.2, U13.6 (OUT)
unnamed: C51.1, U11.4 (RF2)
unnamed: C51.2, U10.2 (RF1)
unnamed: C58.2, U13.3 (IN)
unnamed: C59.2, U25.3 (IN)
unnamed: C61.1, U14.5 (RF2)
unnamed: C61.2, U12.5 (RF2)
unnamed: C62.2, L12.2, U25.6 (OUT)
unnamed: C64.1, U14.1 (RFC)
unnamed: C64.2, D1.2 (K), L13.2, P4.1 (RF)
unnamed: C99.1, L7.1, U17.4 (RXRF+)
unnamed: C99.2, L6.1, T3.4 (PR2)
unnamed: C102.1, L7.2, U17.5 (RXRF-)
unnamed: C102.2, L6.2, T3.3 (PR1)
unnamed: C104.1, L9.1, U17.10 (TXRF+)
unnamed: C104.2, L8.1, T4.4 (PR2)
unnamed: C105.1, FB2.2, NT3.2
unnamed: C106.1, U17.27 (BYPASS)
unnamed: C111.1, L9.2, U17.11 (TXRF-)
unnamed: C111.2, L8.2, T4.3 (PR1)
unnamed: C114.1, R26.2
unnamed: C114.2, R25.2
unnamed: C125.2, R46.2, R47.2, U21.1 (ADJ2)
unnamed: C160.1, C162.2, L12.1, R43.1
unnamed: C52.1, C163.2, L5.1, R42.2
unnamed: D2.2 (A), R18.1
unnamed: D4.2 (A), R72.1
unnamed: D5.2 (A), R73.1
unnamed: D6.2 (A), R74.1
unnamed: D7.2 (A), R75.1
unnamed: D8.2 (A), R76.1
unnamed: D10.1 (K), JP1.1 (A), L13.1
unnamed: D10.2 (A), JP1.2 (B), Q4.3 (D)
unnamed: FB1.1, J1.1 (VBUS)
unnamed: FB2.1, Q3.3 (D)
unnamed: FB3.1, J1.5 (GND)
unnamed: J1.2 (D-), R58.2, U15.3 (ESD2)
unnamed: J1.3 (D+), R57.2, U15.1 (ESD1)
unnamed: J1.4 (ID), P71.1, R12.2, U23.22 (USB0_ID)
unnamed: L1.1, T1.4 (PR2), U4.23 (MIX_IPP)
unnamed: L1.2, T1.3 (PR1), U4.24 (MIX_IPN)
unnamed: L2.1, L4.2, T2.4 (PR2), U4.27 (MIX_OPN)
unnamed: L3.1, L4.1, T2.3 (PR1), U4.28 (MIX_OPP)
unnamed: L10.1, U21.10 (SW2)
unnamed: L11.2, U21.6 (SW1)
unnamed: P6.1, U4.26 (GPO4/LD/DO)
unnamed: P7.1, U4.16 (GPO2/ADD2)
unnamed: P17.1, U4.9 (MODE/GPO6)
unnamed: P19.1, U4.25 (GPO3/FM)
unnamed: P24.1, U23.29 (TRST)
unnamed: Q1.3 (D), R42.1
unnamed: Q2.3 (D), R43.2
unnamed: R4.2, U4.4 (REXT)
unnamed: R19.2, R49.2, SW2.2
unnamed: R7.1, R30.2, SW1.2
unnamed: R51.1, U21.2 (MODE/DATA)
unnamed: R52.2, U21.7 (EN1)
unnamed: R55.2, R56.2, U21.5 (DEF1)
unnamed: R62.1, R65.2, U23.21 (USB0_VBUS)
RSSI: P67.1, U17.32 (RSSI), U23.2 (ADC0_1/ADC1_1)
RX: C24.2, C33.1, C45.2, P43.1, U2.5 (VCTL), U7.5 (VCTL), U10.5 (VCTL), U23.91 (P2_5)
RXENABLE: P56.1, U17.48 (RXENABLE), U23.10 (P4_5)
RX_AMP: C60.2, C66.2, P49.1, U12.3 (V1), U14.7 (V3), U23.105 (P2_11)
RX_IF: C48.2, T3.1 (S1)
RX_MIX_BP: C40.2, P47.1, U9.7 (V3), U23.54 (P5_3)
SCL: P22.26, P37.1, R28.2, U19.4 (SCL), U23.92 (I2C0_SCL)
SDA: P22.24, P38.1, R27.2, U19.5 (SDA), U23.93 (I2C0_SDA)
SGPIO_CLK: C159.1, P60.1, R94.1, U23.72 (P9_6)
SSP1_CIPO: C168.1, P41.1, U17.29 (DOUT), U23.44 (P1_3)
SSP1_COPI: P40.1, U17.31 (DIN), U18.34 (DIN), U23.47 (P1_4)
SSP1_SCK: P39.1, U17.15 (SCLK), U18.35 (SCLK), U23.68 (P1_19)
TXENABLE: P55.1, U17.47 (TXENABLE), U23.9 (P4_4)
TX_AMP: C55.1, C63.1, P48.1, U12.7 (V3), U14.3 (V1), U23.63 (P5_6)
TX_IF: C8.1, T4.1 (S1)
TX_MIX_BP: C39.2, P46.1, U9.3 (V1), U23.46 (P5_2)
VAA: C3.1, C4.1, C5.1, C6.1, C10.2, C16.1, C19.2, C22.2, C30.1, C41.1, C42.1, C53.1, C54.1, C56.1, C71.1, C72.1, C73.1, C74.1, C75.1, C76.1, C77.1, C78.1, C79.1, C80.1, C81.1, C82.1, C83.1, C84.1, C85.1, C86.1, C87.1, C89.1, C90.1, C91.1, C92.1, C93.1, C94.1, C161.1, C166.1, C171.1, L2.2, L3.2, NT3.1, Q1.2 (S), Q2.2 (S), Q4.2 (S), R18.2, R24.2, R29.1, R36.2, U1.1 (VDD), U2.1 (VDD), U4.5 (ANA_VDD1), U4.22 (ANA_VDD2), U5.1 (VDD), U6.1 (VDD), U7.1 (VDD), U10.1 (VDD), U11.1 (VDD), U17.1 (VCCRXLNA), U17.7 (VCCTXPAD), U17.13 (VCCTXMX), U17.19 (VCCXTAL), U17.21 (VCCCP), U17.28 (VCCVCO), U17.39 (VCCRXVGA), U17.41 (VCCRXFL), U17.46 (VCCRXMX), U18.2 (VDD), U18.8 (VDD), U18.11 (VDD), U18.33 (VDD), U18.39 (VDD), U18.43 (VDD), U18.46 (REFIN)
VCC: C1.1, C2.1, C88.1, C113.1, C119.1, C120.1, C121.1, C122.1, C123.1, C124.1, C128.1, C129.1, C130.1, C131.1, C132.1, C133.1, C134.1, C135.1, C137.1, C138.1, C139.1, C140.1, C141.1, C142.1, C144.1, C148.1, C149.1, C150.1, C153.1, C154.1, C167.1, NT2.1, P5.2, P20.3, P22.11, P26.1, P28.1, P30.1, Q3.2 (S), R5.1, R6.1, R11.1, R12.1, R27.1, R28.1, R38.1, R48.1, R49.1, R59.1, R63.2, R64.2, R66.1, R67.2, R75.2, R104.1, R105.1, SW1.1, U4.19 (DIG_VDD), U17.20 (VCCDIG), U18.18 (OVDD), U19.10 (VDDOB), U19.11 (VDDOA), U19.14 (VDDOD), U19.18 (VDDOC), U19.20 (VDD), U20.8 (VCC), U23.5 (VDDIO), U23.16 (USB0_VDDA3V3_DRIVER), U23.17 (USB0_VDDA3V3), U23.25 (VDDREG), U23.36 (VDDIO), U23.41 (VDDIO), U23.59 (VDDREG), U23.71 (VDDIO), U23.77 (VDDIO), U23.94 (VDDREG), U23.107 (VDDIO), U23.111 (VDDIO), U23.131 (VDDREG), U23.136 (ADC0_7/ADC1_7), U23.137 (VDDA), U23.141 (VDDIO), U24.5 (VAUX), U24.38 (VCCIO1), U24.51 (VCCIO1), U24.88 (VCCIO2), U24.98 (VCCIO2)
XCVR_EN: R41.2, U17.25 (ENABLE), U23.11 (P4_6)

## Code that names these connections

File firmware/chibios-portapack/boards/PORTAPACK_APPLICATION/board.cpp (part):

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 * 1V8 supply:
 * Ramps up in about 1ms.
 * EN1V8 has a 10K pull-down on the HackRF and is pulled up (very gently) by the LPC43xx
 * bootloader at boot time. So until the EN1V8 pin is reconfigured as an output, the enable
 * pin on the 1V8 supply sits at about 0.55V, which feels untidy...
 * 1V8 supply is activated when GPIO is driven high by user code.
 */
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        .data
            = (1 << 15) // P1_20: CS_XCVR
            | (1 << 14) // P2_10: AMP_BYPASS
            | (0 << 13) // P1_18: SGPIO12, HOST_Q_INVERT
            | (0 << 12) // P1_17: SGPIO11, HOST_DIRECTION
            | (1 << 11) // P1_4:  SSP1_MOSI
            | (1 << 10) // P1_3:  SSP1_MISO
            | (0 <<  9) // P1_2:  Varies by revision, float until detection
            | (0 <<  8) // P1_1:  Varies by revision, float until detection
            | (0 <<  7) // P2_7:  Varies by revision, float until detection
            | (0 <<  6) // P3_6:  SPIFI_MISO
            | (1 <<  5) // P6_6:  SGPIO5, HOST_DATA5
            | (1 <<  4) // P1_0:  SGPIO7, HOST_DATA7
            | (1 <<  3) // P1_16: SGPIO3, HOST_DATA3
            | (1 <<  2) // P1_15: SGPIO2, HOST_DATA2
            | (1 <<  1) // P0_1:  SGPIO1, HOST_DATA1
            | (1 <<  0) // P0_0:  SGPIO0, HOST_DATA0
            ,
        .dir
            = (1 << 15) // P1_20: CS_XCVR
            | (1 << 14) // P2_10: AMP_BYPASS
            | (1 << 13) // P1_18: SGPIO12, HOST_Q_INVERT
            | (0 << 12) // P1_17: SGPIO11, HOST_DIRECTION
            | (0 << 11) // P1_4:  SSP1_MOSI
            | (0 << 10) // P1_3:  SSP1_MISO
            | (0 <<  9) // P1_2:  Varies by revision, float until detection
            | (0 <<  8) // P1_1:  Varies by revision, float until detection
            | (0 <<  7) // P2_7:  Varies by revision, float until detection
            | (0 <<  6) // P3_6:  SPIFI_MISO
            | (0 <<  5) // P6_6:  SGPIO5, HOST_DATA5
            | (0 <<  4) // P1_0:  SGPIO7, HOST_DATA7
            | (0 <<  3) // P1_16: SGPIO3, HOST_DATA3
            | (0 <<  2) // P1_15: SGPIO2, HOST_DATA2
            | (0 <<  1) // P0_1:  SGPIO1, HOST_DATA1
            | (0 <<  0) // P0_0:  SGPIO0, HOST_DATA0
    },
    {   // GPIO1
        .data
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            | (0 << 10) // P2_9:  10K PD, BOOT3, PortaPack LCD_WRX
            | (1 <<  9) // P1_6:  SD_CMD
            | (1 <<  8) // P1_5:  SD_POW, PortaPack CPLD.TDO(O) (input with pull up)
            | (1 <<  7) // P1_14: SGPIO10, HOST_DISABLE
            | (1 <<  6) // P1_13: SD_CD
            | (1 <<  5) // P1_12: SD_DAT3
            | (1 <<  4) // P1_11: SD_DAT2
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            | (0 << 10) // P2_9:  10K PD, BOOT3, PortaPack LCD_WRX
            | (0 <<  9) // P1_6:  SD_CMD
            | (0 <<  8) // P1_5:  SD_POW, PortaPack CPLD.TDO(O) (input with pull up)
            | (0 <<  7) // P1_14: SGPIO10, HOST_DISABLE
            | (0 <<  6) // P1_13: SD_CD
            | (0 <<  5) // P1_12: SD_DAT3
            | (0 <<  4) // P1_11: SD_DAT2
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            | (0 <<  6) // P4_6:  XCVR_EN, 10K PD
            | (0 <<  5) // P4_5:  RXENABLE
            | (0 <<  4) // P4_4:  Varies by revision, float until detection
            | (1 <<  3) // P4_3:  SGPIO9, HOST_CAPTURE
            | (0 <<  2) // P4_2:  LED2 (RX)
            | (0 <<  1) // P4_1:  LED1 (USB)
            | (1 <<  0) // P4_0:  HP
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            | (1 <<  6) // P4_6:  XCVR_EN, 10K PD
            | (1 <<  5) // P4_5:  RXENABLE
            | (0 <<  4) // P4_4:  Varies by revision, float until detection
            | (0 <<  3) // P4_3:  SGPIO9, HOST_CAPTURE
            | (1 <<  2) // P4_2:  LED2 (RX)
            | (1 <<  1) // P4_1:  LED1 (USB)
            | (1 <<  0) // P4_0:  HP
    },
    {   // GPIO3
        .data
            = (1 << 15) // P7_7:  PortaPack GPIO3_15(IO)
            | (1 << 14) // P7_6:  PortaPack GPIO3_14(IO)
            | (1 << 13) // P7_5:  PortaPack GPIO3_13(IO)
            | (1 << 12) // P7_4:  PortaPack GPIO3_12(IO)
            | (1 << 11) // P7_3:  PortaPack GPIO3_11(IO)
            | (1 << 10) // P7_2:  PortaPack GPIO3_10(IO)
            | (1 <<  9) // P7_1:  PortaPack GPIO3_9(IO)
            | (1 <<  8) // P7_0:  PortaPack GPIO3_8(IO)
            | (1 <<  7) // P6_11: VREGMODE
            | (0 <<  6) // P6_10: Varies by revision, float until detection
            | (1 <<  5) // P6_9:  !TX_AMP_PWR, 10K PU
            | (1 <<  4) // P6_5:  HackRF CPLD.TMS(I) (output only when needed, pull-up internal to CPLD when 1V8 present)
            | (1 <<  3) // P6_4:  MIXER_SDATA
            | (1 <<  2) // P6_3:  SGPIO4, HOST_DATA4
            | (1 <<  1) // P6_2:  HackRF CPLD.TDI(I), PortaPack I2S0_RX_SDA(O), PortaPack CPLD.TDI(I) (output only when needed, pull-up internal to CPLD when 1V8 present)
            | (1 <<  0) // P6_1:  HackRF CPLD.TCK(I), PortaPack CPLD.TCK(I) (output only when needed, pull-up internal to CPLD when 1V8 present)
            ,
        .dir
            = (0 << 15) // P7_7:  PortaPack GPIO3_15(IO)
            | (0 << 14) // P7_6:  PortaPack GPIO3_14(IO)
            | (0 << 13) // P7_5:  PortaPack GPIO3_13(IO)
            | (0 << 12) // P7_4:  PortaPack GPIO3_12(IO)
            | (0 << 11) // P7_3:  PortaPack GPIO3_11(IO)
            | (0 << 10) // P7_2:  PortaPack GPIO3_10(IO)
            | (0 <<  9) // P7_1:  PortaPack GPIO3_9(IO)
            | (0 <<  8) // P7_0:  PortaPack GPIO3_8(IO)
            | (1 <<  7) // P6_11: VREGMODE
            | (0 <<  6) // P6_10: Varies by revision, float until detection
            | (1 <<  5) // P6_9:  !TX_AMP_PWR, 10K PU
            | (0 <<  4) // P6_5:  HackRF CPLD.TMS(I) (output only when needed, pull-up internal to CPLD when 1V8 present)
            | (0 <<  3) // P6_4:  MIXER_SDATA
            | (0 <<  2) // P6_3:  SGPIO4, HOST_DATA4
            | (0 <<  1) // P6_2:  HackRF CPLD.TDI(I), PortaPack I2S0_RX_SDA(O), PortaPack CPLD.TDI(I) (output only when needed, pull-up internal to CPLD when 1V8 present)
            | (0 <<  0) // P6_1:  HackRF CPLD.TCK(I), PortaPack CPLD.TCK(I) (output only when needed, pull-up internal to CPLD when 1V8 present)
    },
    {   // GPIO4
        .data
            = (1 << 11) // P9_6:  SGPIO8, SGPIO_CLK
            ,
        .dir
            = (0 << 11) // P9_6:  SGPIO8, SGPIO_CLK
    },
    {   // GPIO5
        .data
            = (1 << 18) // P9:5:  HackRF CPLD.TDO(O) (input with pull up)
            | (1 << 16) // P6_8:  MIX_BYPASS
            | (0 << 15) // P6_7:  Varies by revision, float until detection
            | (1 << 14) // P4_10: SGPIO15, CPLD (unused)
            | (1 << 13) // P4_9:  SGPIO14, CPLD (unused)
            | (0 << 12) // P4_8:  Varies by revision, float until detection
            | (1 << 11) // P3_8:  SPIFI_CS
            | (1 << 10) // P3_7:  SPIFI_MOSI
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            | (0 <<  5) // P2_5:  Varies by revision, float until detection
            | (1 <<  4) // P2_4:  PortaPack LCD_RDX
            | (0 <<  3) // P2_3:  PortaPack LCD_TE
            | (1 <<  2) // P2_2:  SGPIO6, HOST_DATA6
            | (0 <<  1) // P2_1:  PortaPack ADDR
            | (1 <<  0) // P2_0:  PortaPack IO_STBX
            ,
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            = (0 << 18) // P9_5:  HackRF CPLD.TDO(O) (input with pull up)
            | (1 << 16) // P6_8:  MIX_BYPASS
            | (0 << 15) // P6_7:  Varies by revision, float until detection
            | (0 << 14) // P4_10: SGPIO15, CPLD (unused)
            | (0 << 13) // P4_9:  SGPIO14, CPLD (unused)
            | (0 << 12) // P4_8:  Varies by revision, float until detection
            | (0 << 11) // P3_8:  SPIFI_CS
            | (0 << 10) // P3_7:  SPIFI_MOSI
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            | (0 <<  5) // P2_5:  Varies by revision, float until detection
            | (0 <<  4) // P2_4:  PortaPack LCD_RDX
            | (0 <<  3) // P2_3:  PortaPack LCD_TE
            | (0 <<  2) // P2_2:  SGPIO6, HOST_DATA6
            | (0 <<  1) // P2_1:  PortaPack ADDR
            | (0 <<  0) // P2_0:  PortaPack IO_STBX
    },
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    {  6,  9, scu_config_normal_drive_t { .mode=0, .epd=0, .epun=1, .ehs=0, .ezi=0, .zif=0 } }, /* !TX_AMP_PWR/P51: 10K PU, Q2.G(I), power to U25 (TX amp) */

    /* SGPIO for sample transfer interface to HackRF CPLD. */
    {  0,  0, scu_config_normal_drive_t { .mode=3, .epd=0, .epun=1, .ehs=1, .ezi=1, .zif=1 } }, /* SGPIO0/P75/BANK2F3M3: CPLD.89/HOST_DATA0(IO) */
    {  0,  1, scu_config_normal_drive_t { .mode=3, .epd=0, .epun=1, .ehs=1, .ezi=1, .zif=1 } }, /* SGPIO1/BANK2F3M5: CPLD.79/HOST_DATA1(IO) */
    {  1, 15, scu_config_normal_drive_t { .mode=2, .epd=0, .epun=1, .ehs=1, .ezi=1, .zif=1 } }, /* SGPIO2/BANK2F3M9: CPLD.74/HOST_DATA2(IO) */
    {  1, 16, scu_config_normal_drive_t { .mode=2, .epd=0, .epun=1, .ehs=1, .ezi=1, .zif=1 } }, /* SGPIO3/BANK2F3M10: CPLD.72/HOST_DATA3(IO) */
    {  6,  3, scu_config_normal_drive_t { .mode=2, .epd=0, .epun=1, .ehs=1, .ezi=1, .zif=1 } }, /* SGPIO4/BANK2F3M14: CPLD.67/HOST_DATA4(IO) */
    {  6,  6, scu_config_normal_drive_t { .mode=2, .epd=0, .epun=1, .ehs=1, .ezi=1, .zif=1 } }, /* SGPIO5/BANK2F3M15: CPLD.64/HOST_DATA5(IO) */
    {  2,  2, scu_config_normal_drive_t { .mode=0, .epd=0, .epun=1, .ehs=1, .ezi=1, .zif=1 } }, /* SGPIO6/BANK2F3M16: CPLD.61/HOST_DATA6(IO) */
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
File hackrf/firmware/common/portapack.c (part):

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}

// clang-format off
static struct gpio_t gpio_io_stbx = GPIO(5,  0); /* P2_0 */
static struct gpio_t gpio_addr    = GPIO(5,  1); /* P2_1 */
__attribute__((unused))
static struct gpio_t gpio_lcd_te  = GPIO(5,  3); /* P2_3 */
__attribute__((unused))
static struct gpio_t gpio_unused  = GPIO(5,  7); /* P2_8 */
static struct gpio_t gpio_lcd_rdx = GPIO(5,  4); /* P2_4 */
static struct gpio_t gpio_lcd_wrx = GPIO(1, 10); /* P2_9 */
static struct gpio_t gpio_dir     = GPIO(1, 13); /* P2_13 */

// clang-format on

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
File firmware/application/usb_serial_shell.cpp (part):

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
    if (strncmp(argv[0], "hackrf", 5) == 0) {
        jtag::GPIOTarget jtag_target_hackrf_cpld{
            hackrf::one::gpio_cpld_tck,
            hackrf::one::gpio_cpld_tms,
            hackrf::one::gpio_cpld_tdi,
            hackrf::one::gpio_cpld_tdo,
        };

        hackrf::one::cpld::CPLD hackrf_cpld{jtag_target_hackrf_cpld};
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
    } else if (strncmp(argv[0], "portapack", 5) == 0) {
        jtag::GPIOTarget target{
            portapack::gpio_cpld_tck,
            portapack::gpio_cpld_tms,
            portapack::gpio_cpld_tdi,
            portapack::gpio_cpld_tdo};
        jtag::JTAG jtag{target};
        portapack::cpld::CPLD cpld{jtag};

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    if (strncmp(argv[0], "hackrf", 5) == 0) {
        if (strncmp(argv[1], "eeprom", 5) == 0) {
            jtag::GPIOTarget jtag_target_hackrf_cpld{
                hackrf::one::gpio_cpld_tck,
                hackrf::one::gpio_cpld_tms,
                hackrf::one::gpio_cpld_tdi,
                hackrf::one::gpio_cpld_tdo,
            };

            hackrf::one::cpld::CPLD hackrf_cpld{jtag_target_hackrf_cpld};
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
        else if (strncmp(argv[1], "sram", 5) == 0) {
            jtag::GPIOTarget jtag_target_hackrf_cpld{
                hackrf::one::gpio_cpld_tck,
                hackrf::one::gpio_cpld_tms,
                hackrf::one::gpio_cpld_tdi,
                hackrf::one::gpio_cpld_tdo,
            };

            hackrf::one::cpld::CPLD hackrf_cpld{jtag_target_hackrf_cpld};
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        }
    } else if (strncmp(argv[0], "portapack", 5) == 0) {
        jtag::GPIOTarget target{
            portapack::gpio_cpld_tck,
            portapack::gpio_cpld_tms,
            portapack::gpio_cpld_tdi,
            portapack::gpio_cpld_tdo};
        jtag::JTAG jtag{target};
        portapack::cpld::CPLD cpld{jtag};

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    } else if (strncmp(argv[0], "portapack", 5) == 0) {
        if (strncmp(argv[1], "eeprom", 5) == 0) {
            jtag::GPIOTarget target{
                portapack::gpio_cpld_tck,
                portapack::gpio_cpld_tms,
                portapack::gpio_cpld_tdi,
                portapack::gpio_cpld_tdo};
            jtag::JTAG jtag{target};
            portapack::cpld::CPLD cpld{jtag};

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
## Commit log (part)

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2025-11-29 1MB code
2025-11-29 2MB code
2026-05-31 add low power mode

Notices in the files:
firmware/application/usb_serial_shell.cpp:
Copyright (C) 2023 Bernd Herzog
This program is free software; you can redistribute it and/or modify
it under the terms of the GNU General Public License as published by
the Free Software Foundation; either version 2, or (at your option)
firmware/chibios-portapack/boards/PORTAPACK_APPLICATION/board.cpp:
ChibiOS/RT - Copyright (C) 2006-2013 Giovanni Di Sirio
Copyright (C) 2014 Jared Boone, ShareBrained Technology
Licensed under the Apache License, Version 2.0 (the "License");
